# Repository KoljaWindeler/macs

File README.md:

please refere to http://koljawindeler.github.io/macs

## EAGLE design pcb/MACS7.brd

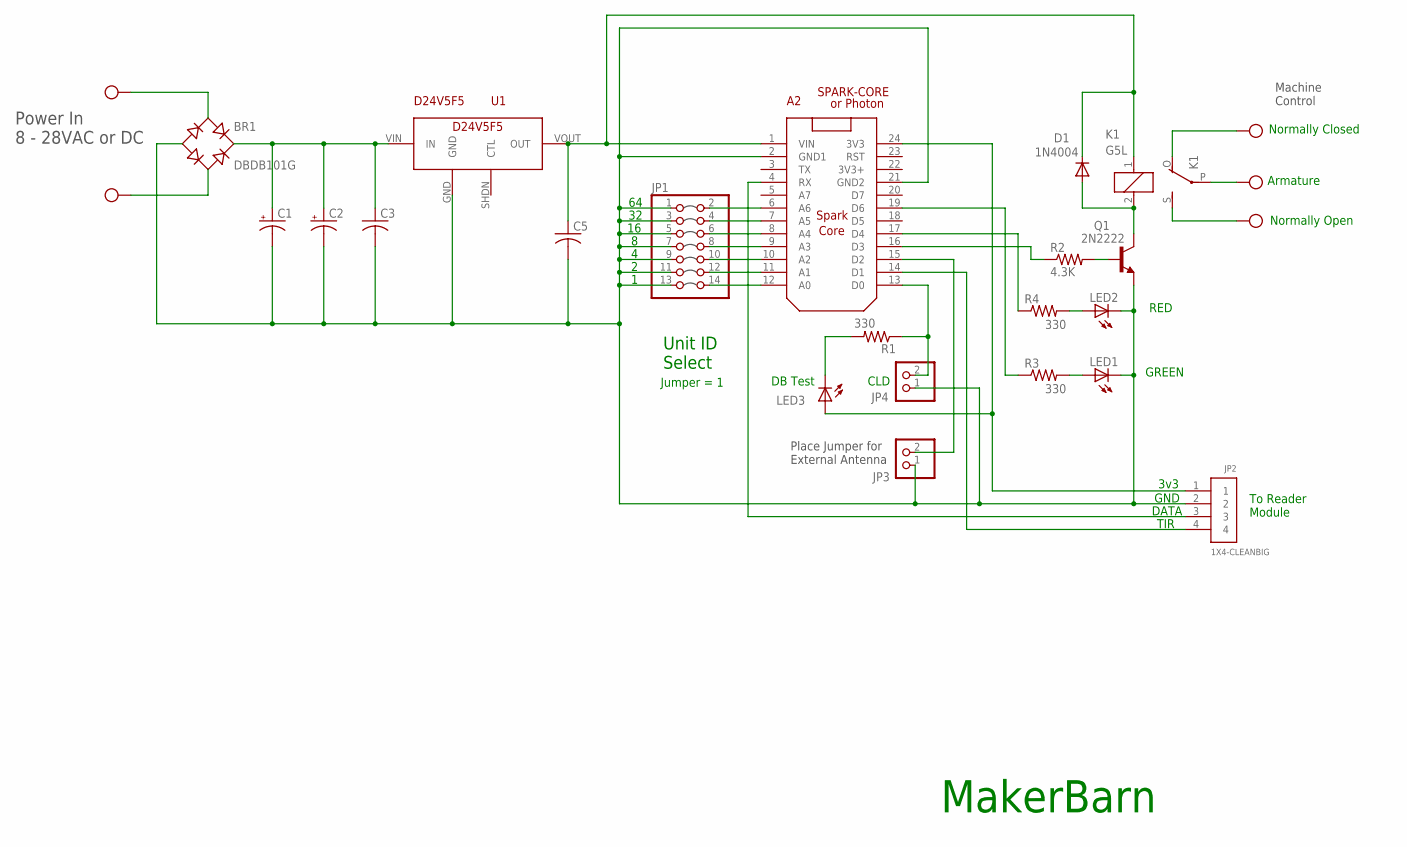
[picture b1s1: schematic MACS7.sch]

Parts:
A2: SPARK-CORE
BR1: DBDB101G; DB
C1, C2: CPOL-USE35-16AXIAL; E35-16
C3, C5: C-US050-035X075; C050-035X075
D1: 1N4004; DO41-10
JP1: PINHD-2X7; 2X07
JP2: 1X4-CLEANBIG; 1X04-CLEANBIG
JP3, JP4: PINHD-1X2; 1X02
K1: G5L; G5LE
LED1, LED2: LED5MM
LED3: LED3MM
Q1: 2N2222; TO92-EBC-OVAL
R1, R3, R4: 330; R0805
R2: 4.3K; R0805
U1: D24V5F5; POLOLUREG
X2: MKDSN1,5/2-5,08
X3: MKDSN1,5/3-5,08

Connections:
3V3: A2.24 (3V3), JP2.1, LED3.A
DATA: A2.4 (RX), JP2.3
GND: A2.2 (GND1), A2.21 (GND2), BR1.-, C1.-, C2.-, C3.2, C5.2, JP1.1, JP1.3, JP1.5, JP1.7, JP1.9, JP1.11, JP1.13, JP2.2, JP3.1, JP4.1, LED1.K (C), LED2.K (C), Q1.E, U1.GND
unnamed: K1.P, X3.1
unnamed: A2.16 (D3), R2.1
unnamed: A2.6 (A6), JP1.2
unnamed: BR1.AC2, X2.2
unnamed: A2.1 (VIN), C5.1, D1.C, K1.1, U1.VOUT (OUT)
unnamed: BR1.AC1, X2.1
unnamed: A2.17 (D4), R4.1
unnamed: A2.19 (D6), R3.1
unnamed: LED2.A, R4.2
unnamed: LED1.A, R3.2
unnamed: K1.O, X3.2
unnamed: Q1.B, R2.2
unnamed: A2.7 (A5), JP1.4
unnamed: D1.A, K1.2, Q1.C
unnamed: BR1.+, C1.+, C2.+, C3.1, U1.VIN (IN)
unnamed: K1.S, X3.3
unnamed: A2.8 (A4), JP1.6
unnamed: A2.9 (A3), JP1.8
unnamed: A2.10 (A2), JP1.10
unnamed: A2.11 (A1), JP1.12
unnamed: A2.12 (A0), JP1.14
unnamed: A2.15 (D2), JP3.2
unnamed: A2.13 (D0), JP4.2, R1.1
unnamed: LED3.K (C), R1.2
TIR: A2.14 (D1), JP2.4

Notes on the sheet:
TIR
3v3
DATA
GND
Normally Open
Normally Closed
Armature
Unit ID Select
Jumper = 1
Power In 8 - 28VAC or DC
or Photon
Place Jumper for External Antenna
Machine Control
To Reader Module
MakerBarn
RED
GREEN
DB Test
CLD

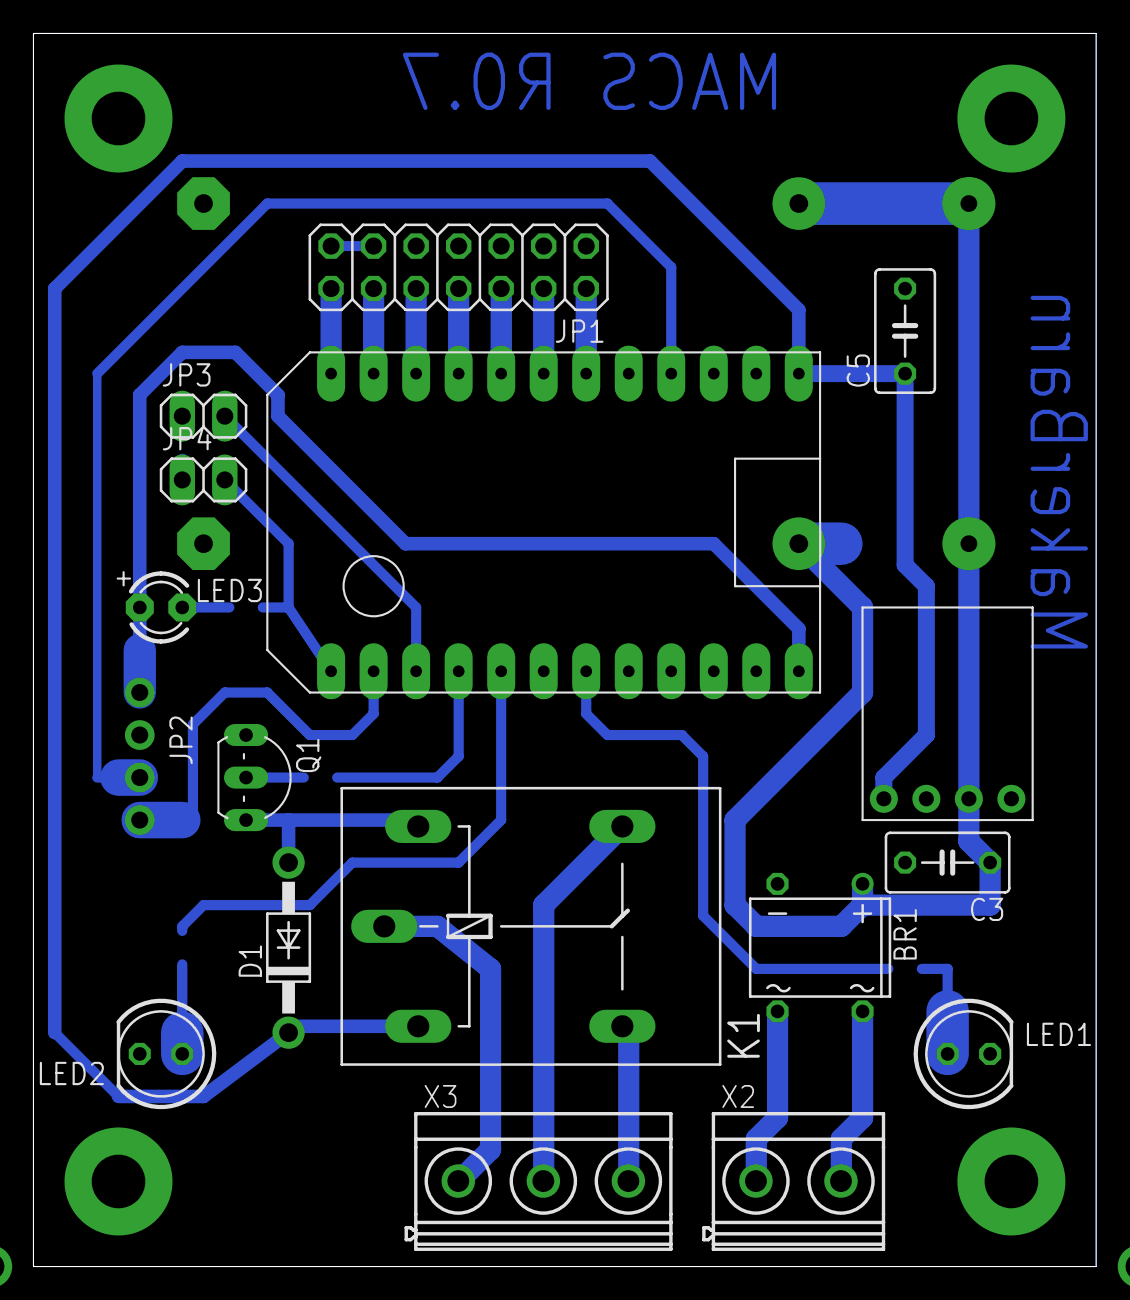
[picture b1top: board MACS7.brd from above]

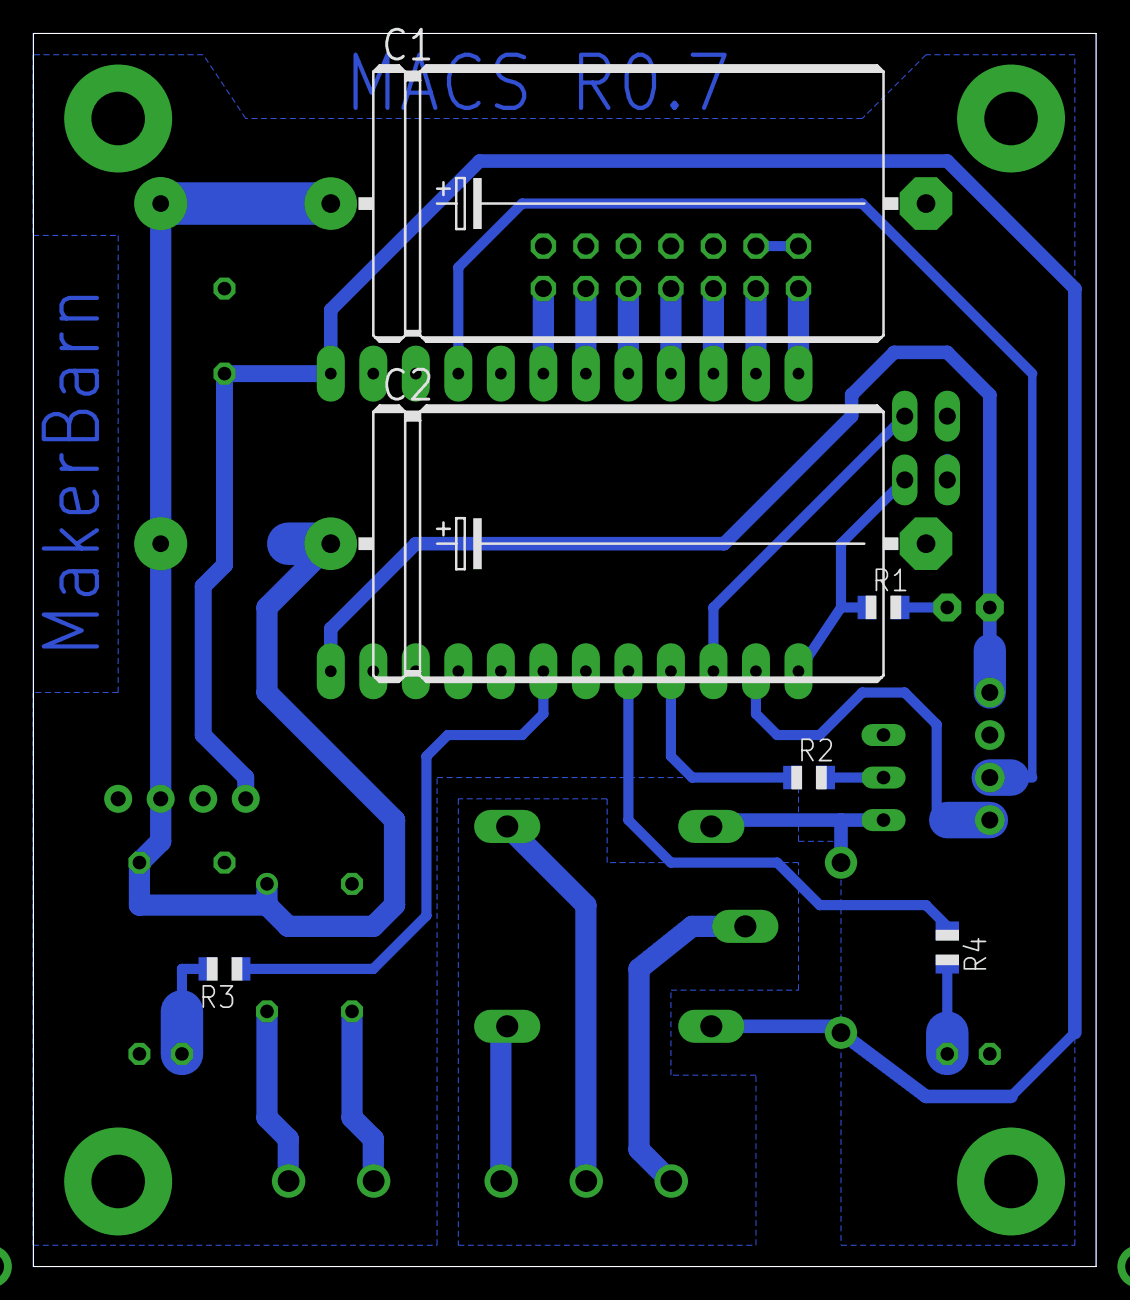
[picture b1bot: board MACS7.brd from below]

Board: 2 copper layers, 63.5 x 73.7 mm, 23 parts (6 on the bottom side), 28 nets.

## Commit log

2015-10-01 init
2015-10-01 Added sql dump
2015-10-03 limited mach name to 12 chars, check if desc, id and name a present
2015-10-03 free mach_id when delete machine to reuse it
2015-10-03 avoid error on delte machine in log
2015-10-03 changed lock to station
2015-10-03 auto clear '-' from field on mouse click
2015-10-03 added check to field, after editing a user/mach that existed
2015-10-03 added range check for mach id
2015-10-03 added log entry every time the station updates
2015-10-03 change mach_id to mach_nr
2015-10-03 added 'update_available' check
2015-10-03 machine is only creating a log entry if something has changed
2015-10-03 added machine-ready-to-update function
2015-10-03 set machine-ready-to-update if anything in connection with the machine changes
2015-10-03 backup alpha 0.1
2015-10-03 updating machine will update last_seen of machine
2015-10-03 request for deleting entry added
2015-10-03 login alpha 0.1
2015-10-03 added tracking for who modified what
2015-10-03 added tracking for logging
2015-10-03 highlight line
2015-10-04 limited highlight function to cells with content
2015-10-04 changing label of buttons from add to update on an update
2015-10-04 extended popup to 5 sec
2015-10-04 avoid login from deleted users
2015-10-04 added timezone corrected dates
2015-10-04 jump to log
2015-10-04 Changed keys to 11byte, add serial.read instead of simulation
2015-10-05 corrected argument attachment
2015-10-05 Removed unused css code
2015-10-06 changed server password
2015-10-06 added lookup for right user id by badge and machine by machine nr
2015-10-06 added check if machine id in range
2015-10-06 allow multiple user with same login
2015-10-06 resolve internet dependencies
2015-10-06 current db dump
2015-10-06 updated time
2015-10-06 firmware updated
2015-10-07 added changing backgrounds
2015-10-07 added usage
2015-10-07 avoid empty background
2015-10-07 unset background on logout
2015-10-07 added sorting for table and 'info' column
2015-10-09 added email check and badge id
2015-10-10 added standalone loginless logviewer
2015-10-10 modularized logs
2015-10-10 moved log to external module
2015-10-10 improved tz
2015-10-10 removed white bg
2015-10-10 erase leading 0
2015-10-10 check empty md5 string
2015-10-10 new box size
2015-10-10 added tailing comma
2015-11-03 removed leading zero
2015-11-03 removed leading zeros
2015-11-03 removed bright bg images
2015-11-03 updated firmware BETA 1
2015-11-03 removed bg4,5,6
2015-11-05 fixed host
2015-11-07 fixed ngix header
2015-11-07 incread range from 64 to 128 machines
2015-11-07 added show unknown machines in log
2015-11-07 fix logging without timezone
2015-11-07 Create gh-pages branch via GitHub
2015-11-07 added ignore for gh-page
2015-11-07 added version 7 of pcb
2015-11-07 inital docu
2015-11-07 added photo on top
2015-11-07 added link to gh page
2015-11-07 resized images
2015-11-07 added panel disclaimer
2015-11-09 centralized state processing
2015-11-09 handle unconnected network
2015-11-09 removed debug
2015-11-11 added history functionality
2015-11-12 fixed typos
2015-11-12 heavy card waiving was leading to an LED error
2015-11-15 removed wait states to speed reports up
2015-11-15 added hw_off to clear to reset the led state
2015-11-15 Added antenna selection to main code
2015-11-15 added usage module
2015-11-15 added jscharts towebsite
2015-11-15 add usage module to dashboard
2015-11-16 replaced flush(), it didn't flush the input as expected
2015-11-16 removed comments
2015-11-19 no update function added
2015-11-19 separated debug
2015-11-19 separated config in own file
2015-11-19 added read wifi login from serial, from EEPROM and save and validate data
2015-11-19 removed debug msg
2015-11-19 avoid overrun of buffer with uint8_t
2015-11-19 Increase index type:keys can go >256 now, 16bit required
2015-11-19 added python config app
2015-11-24 added wifi scanning
2015-11-26 added blink pattern
2015-11-26 only reconnect if wifi is down
2015-11-26 default config
2015-11-26 multi device, multiple networks
2015-11-27 added comment
2015-11-27 added setup module
2015-11-27 avoid reading var that does not exists
2015-11-27 added design for iframe, basically a copy
2015-11-27 added ajax reader
2015-11-27 moved python to website folder
2015-11-27 fixed logging fkt
2015-11-27 gathered all files in a single config
2015-11-27 added clear
2015-11-27 added parse_wifi to read new data everywhere
2015-11-27 moved to central h file
2015-11-27 removed unneeded files
2015-12-01 changed path of config file
2015-12-01 unified connect to wifi method
2015-12-01 unified connect method
2015-12-01 unified update method
2015-12-01 hide usage and setup by default
2015-12-01 relocate browser to be able to hit f5 for refresh
2015-12-02 added listen to system events to prevent the listen mode
2015-12-02 added listen mode prevention
2015-12-05 Added log cleaner to avoid dual entries
2015-12-05 usage and setup, start closed
2015-12-05 move to index.php to avoid resubmit form
2015-12-05 start log in id sorting mode
2015-12-20 removed timestamp correction
2015-12-20 added backlog
2015-12-22 added version reporting
2015-12-22 removed tz
2015-12-22 added version display
2015-12-22 added version update
2015-12-22 fixed type 4
2016-01-02 added backup, fixed edit mach and user
2016-01-02 add is wifi connected
2016-01-02 added goto update mode on magic key
2016-01-02 added magic key
2016-01-02 added log backup
2016-01-10 6 to 10 digits
2016-02-14 removed timezone
2016-02-14 manual time calc
2016-02-14 enforce LED update after reconnect
2016-02-14 switched to original http client, changed gateway, moved debug to serial1
2016-06-20 added current db struct and dummy login
2016-06-20 renamed con.php to db_con.php
